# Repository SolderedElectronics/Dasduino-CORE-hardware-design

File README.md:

# Dasduino CORE Hardware Design

## About the Product

|  |
| :----------------------------------------------------------: |
| [Buy Dasduino CORE](https://www.solde.red/333037) |

Are you looking to start tinkering with electronics and Arduinos? Or perhaps you’re looking for a board to help you with electronic projects? Dasduino Core is the right choice for you. If you’re familiar with any of the retired Croduino products, you’ll feel right at home with this board. If not, no worries! Dasduino Core is made for makers of all skill levels! Not only will it execute the tasks in a breeze, but it will take up little space while doing so.

With just 63 mm wide and 22 mm high, Dasduino Core packs 22 I/O pins. It has 14 digital and 8 analog pins, which is plenty for almost all projects. It comes with a USB Type-C connection and is 100% compatible with the original Arduino boards and Arduino IDE. It comes with the Atmel Atmega328P microcontroller we all know and love. It works on 5V or battery voltage. There is also a 3.3V voltage regulator on the board for easy powering of 3.3V breakouts or qwiic boards. Furthermore, it features Lithium-ion battery charger and connector, and a full color WS2812 RGB LED. An qwiic connector will make connecting the Dasduino Core with other devices effortless.

---

## Repository Contents

This repository contains all design files for Dasduino CORE, organized as follows:

- **`CAD` folder**: Contains KiCAD design files, including:
  - Schematics
  - PCB layout
  - Panel PCB layout
  - Source 3D files in Fusion360, if any
  - All files are sorted by version with a detailed change log.
- **`OUTPUTS` folder**: Includes all production-ready files, such as:
  - Bill of Materials (BOM) and interactive BOM (iBOM)
  - PDF versions of schematics
  - 3D `.step` file of the board
  - 3D-printable models
  - Gerber files for PCB manufacturing
  - Image of the pinout of the board
  - Product image
  - Compliance, legal and generic sales documents

Refer to the `Change Log` in the CAD folder for details about updates between versions.

---

## Learn More About the Product

Beyond the repository, explore the following resources:

### Soldered Verify

The **Soldered Verify** system ensures every board you purchase from Soldered is fully functional. It also provides access to exclusive test data for your product. To get started, find the unique Soldered Verify ID on your product's packaging and enter the ID on the [Soldered Verify page](https://soldered.com/verify/) to access test results and additional product details.

### Soldered Community

Soldered Community is your go-to place for technical support. Our engineers track and answer all questions posted there, and it’s a great space for the maker community. Get answers to your questions and solutions for your challenges at [Soldered Community](https://soldered.com/community).

### solde.red

solde.red is an ultimate URL shortener and information hub. Access it by typing solde.red/ followed by your product SKU, e.g., [solde.red/333000](https://solde.red/333000), to find getting-started guides, datasheets, open-source hardware and software files, certifications, images, pinouts, and more. Read more about the shortener [here](https://solde.red/info/).

---

## Contributing

Contributions are welcome! Here’s how you can get involved:

- Submit pull requests to enhance the design or fix issues.
- Report bugs or problems by opening an issue.

We encourage community collaboration to make this product even better.

---

## About Soldered

[Soldered for Makers](https://soldered.com) specializes in designing and manufacturing electronic products tailored for enthusiasts, ranging from hobbyists to professionals. Our portfolio includes electronic boards, sensors, and actuators that are widely utilized in fields such as microelectronics, mechatronics, robotics, programming, and IoT. Every product we offer is designed in-house and built upon open-source hardware and software platforms. Proudly certified and manufactured within the European Union, our catalog likely includes the product you need for your project.

We complement these products with comprehensive tutorials and manuals, product descriptions, schematics, programming codes, and project examples. Our round-the-clock [customer and technical support](https://soldered.com/community) is available for all our products, irrespective of the sales channel. Soldered’s success and services reflect our maker community’s unwavering [trust](https://www.trustpilot.com/review/soldered.com), for which we are deeply grateful. Join our community and create using Soldered products.

---

## License

All Soldered open-source hardware (OSH) is under The TAPR Open Hardware License. Read more in the LICENSE file located in this repository.

**Disclaimer:**

No warranty - all designs in this repository are distributed in the hope that they will be useful, but without any warranty. They are provided "AS IS", therefore without warranty of any kind, either expressed or implied. The entire quality and performance of what you do with the contents of this repository are your responsibility. In no event Soldered Electronics will be liable for your damages, or losses, including any general, special, incidental, or consequential damage arising out of the use or inability to use the contents of this repository. 

---

## Have fun!

Thank you for your support from your fellow makers at Soldered Electronics.

Happy Making!

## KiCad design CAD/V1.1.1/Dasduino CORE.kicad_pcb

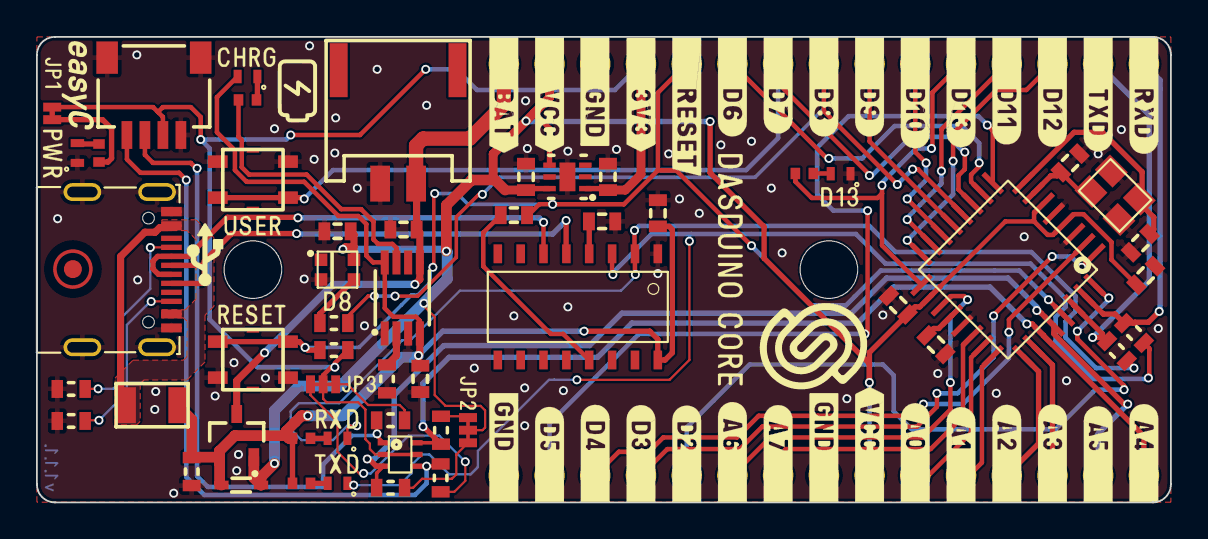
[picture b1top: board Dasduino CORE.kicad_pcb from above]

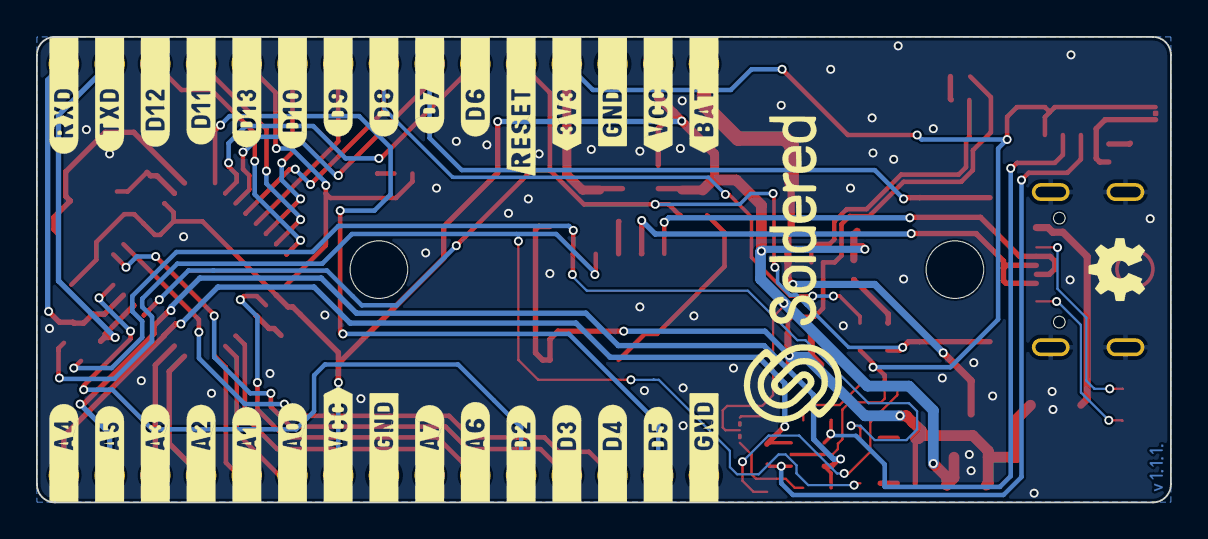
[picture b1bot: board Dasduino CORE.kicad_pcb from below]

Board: 2 copper layers, 63.0 x 25.9 mm, 58 parts (2 on the bottom side), 55 nets.

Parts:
C1, C2: 0.1uF; 0603C
C3, C5, C7, C8: 2.2uF; 0603C
C4, C6, C11, C12, C13: 100nF; 0603C
C9, C10: 22pF; 0603C
D1: blue; 0402LED
D2: white; 0402LED
D3: purple; 0402LED
D4: WS2812B-2020
D5: red; 0402LED
D6: orange; 0402LED
D7: BAT20J; SOD-323
F1: 1206FUSE-500mA; 1206FUSE
FD1: FIDUCIAL; FIDUCIAL_23
H1, H2: HOLE_3.2mm
JP1: SMD-JUMPER-CONNECTED_TRACE_SLODERMASK
JP2, JP3: SMD_JUMPER_3_PAD_TRACE
K1: easyC-SMD; easyC-connector
K2: U262-161N-4BVC11
K3: JST-2pin-SMD
K4, K5: HEADER_MALE_15X1
Q1: PMOS-SOT-23-3; SOT-23-3
R1, R2, R5: 1k; 0603R
R3, R4, R6, R9, R12: 2k2; 0402R
R7, R8: 5.1k; 0603R
R10, R13, R15, R16, R17: 10k; 0603R
R11: 3k; 0603R
R14: 100k; 0603R
SW1, SW2: YTSA007A0151803B
U1: CH340C; SOP-16
U2: TPS7A2633DRVR
U3: TP4056M; TP4056M-MSOP8
U4: ATMEGA_328P
U5: NMOS-DUAL; SOT-363
X1: 16MHz; CRYSTAL_3225__4_PAD

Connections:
+3V3: C5.2, JP1.1, JP3.2, K1.3 (3V3), K4.4, R10.2, U2.1 (OUT), U5.2 (G2), U5.5 (G1)
A0: K5.10, U4.23 (PC0)
A1: K5.11, U4.24 (PC1)
A2: K5.12, U4.25 (PC2)
A3: K5.13, U4.26 (PC3)
A6: K5.6, U4.19 (ADC6)
A7: K5.7, U4.22 (ADC7)
CH-RXD: D1.2 (K), R2.1, U1.3 (RXD)
CH-TXD: D2.2 (K), R1.1, U1.2 (TXD)
D2: K5.5, U4.32 (PD2)
D3: K5.4, U4.1 (PD3)
D4: K5.3, U4.2 (PD4)
D5: K5.2, U4.9 (PD5)
D6: K4.6, U4.10 (PD6)
D7: K4.7, SW1.2, U4.11 (PD7)
D8: K4.8, R5.1, U4.12 (PB0)
D9: K4.9, U4.13 (PB1)
D10: K4.10, U4.14 (PB2)
D11: K4.12, U4.15 (PB3)
D12: K4.13, U4.16 (PB4)
D13: K4.11, R9.1, U4.17 (PB5)
D+: K2.A6 (DP1), K2.B6 (DP2), U1.5 (UD+)
D-: K2.A7 (DN1), K2.B7 (DN2), U1.6 (UD-)
DTR: C11.1, U1.13 (DTR#)
GND: C1.1, C2.2, C3.1, C4.2, C5.1, C6.1, C7.1, C8.1, C9.1, C10.2, C12.1, C13.2, D3.2 (K), D4.2 (GND), D6.2 (K), K1.4 (GND), K1.5 (SHIELD), K2.A1 (GND), K2.A12 (GND), K2.B1 (GND), K2.B12 (GND), K2.SH (SHIELD), K3.2 (-), K4.3, K5.1, K5.8, R7.2, R8.2, R11.2, R14.1, SW1.1, SW2.2, U1.1 (GND), U2.5 (GND), U3.1 (TEMP), U3.3 (GND), U4.3 (GND), U4.5 (GND), U4.21 (GND), X1.2, X1.4
unnamed: C2.1, U1.4 (V3)
unnamed: C13.1, U4.20 (AREF)
unnamed: D1.1 (A), R3.1
unnamed: D2.1 (A), R4.1
unnamed: D3.1 (A), R6.2
unnamed: D4.3 (DI), R5.2
unnamed: D5.2 (K), R12.2
unnamed: D6.1 (A), R9.2
unnamed: F1.2, K2.A4 (VBUS), K2.A9 (VBUS), K2.B4 (VBUS), K2.B9 (VBUS)
unnamed: JP1.2, R6.1
unnamed: K2.A5 (CC1), R8.1
unnamed: K2.B5 (CC2), R7.1
unnamed: R11.1, U3.2 (PROG)
unnamed: R12.1, U3.7 (~CHRG)
RESET: C11.2, K4.5, R10.1, SW2.1, U4.29 (PC6)
RXD: K4.15, R2.2, U4.31 (PD1)
SCL: K1.1 (SCL), R17.1, U5.4 (S1)
SCL_5V: K5.14, R15.2, U4.28 (PC5), U5.3 (D1)
SCL_PULL3,3: JP3.1, R17.2
SCL_PULL5: JP2.1, R15.1
SDA: K1.2 (SDA), R13.2, U5.1 (S2)
SDA_5V: K5.15, R16.1, U4.27 (PC4), U5.6 (D2)
SDA_PULL3,3: JP3.3, R13.1
SDA_PULL5: JP2.3, R16.2
TXD: K4.14, R1.2, U4.30 (PD0)
VBAT: C7.2, K3.1 (+), K4.1, Q1.3 (D), U3.5 (BAT)
VCC: C3.2, C4.1, C6.2, C12.2, D4.4 (VDD), D7.2 (K), JP2.2, K4.2, K5.9, Q1.2 (S), U2.4 (EN), U2.6 (IN), U4.4 (VCC), U4.6 (VCC), U4.18 (AVCC)
VUSB: C1.2, C8.2, D5.1 (A), D7.1 (A), F1.1, Q1.1 (G), R3.2, R4.2, R14.2, U1.16 (VCC), U3.4 (VCC), U3.8 (CE)
XTAL1: C9.2, U4.7 (PB6), X1.3
XTAL2: C10.1, U4.8 (PB7), X1.1

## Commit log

2022-08-06 Updating open source files.
